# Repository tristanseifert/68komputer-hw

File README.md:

# 68komputer Hardware
Hardware designs for the 68komputer.

You can find the related software [in this repository.](https://github.com/tristanseifert/68komputer-sw)

## Old stuff
The 68008-based design I [wrote about](https://blraaz.me/hardware/2019/11/01/68komputer-it-lives.html) and some other stuff has been moved to the `old` directory. Unfortunately, those designs were done using Cadsoft EAGLE, and I no longer have access to my license for it. There are likely hardware bugs I have no way of fixing. Yay!

## License
The contents of this repo are available under the ISC license.

Previously, the material in the `old` directory was BSD licensed; you can continue to use it under the terms of this license.

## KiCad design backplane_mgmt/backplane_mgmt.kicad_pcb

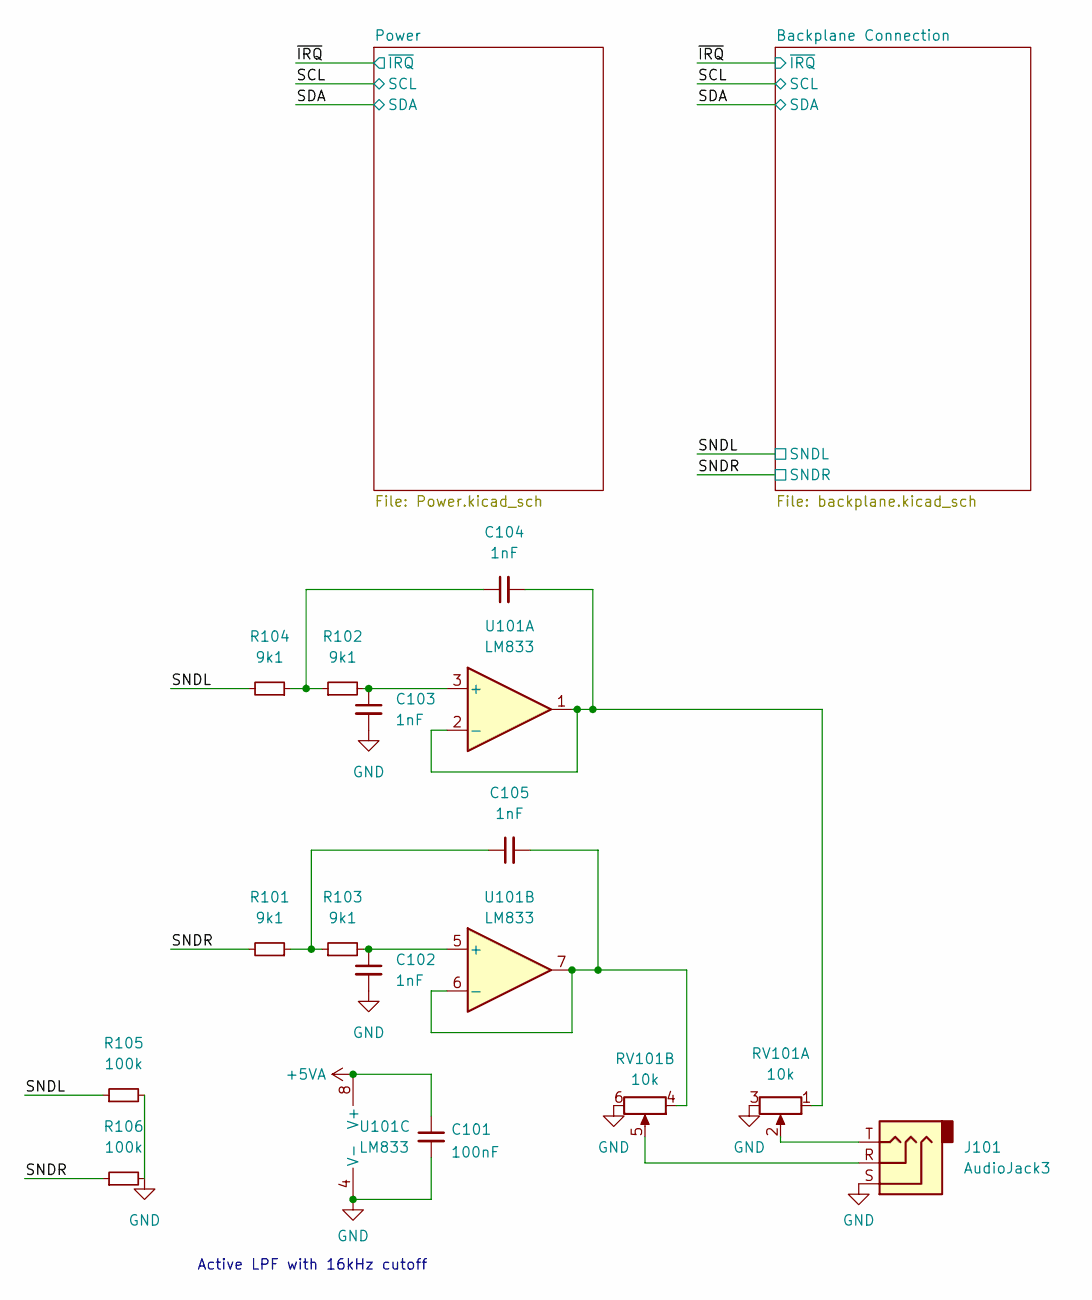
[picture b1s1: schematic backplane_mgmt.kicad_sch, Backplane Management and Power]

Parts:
C101: 100nF; C_0805_2012Metric
C102, C103, C104, C105: 1nF; C_Rect_L7.2mm_W2.5mm_P5.00mm_FKS2_FKP2_MKS2_MKP2; MPN B32529C1102J
J101: AudioJack3; Jack_3.5mm_CUI_SJ1-3533NG_Horizontal; MPN SJ1-3533NG
R101, R102, R103, R104: 9k1; R_0805_2012Metric
R105, R106: 100k; R_0805_2012Metric
RV101: 10k; Potentiometer_Alps_RK097_Dual_Horizontal
U101: LM833; DIP-8_W7.62mm_Socket

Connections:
+5VA: C101.1, U101.8 (V+); also elsewhere on the board
/SNDL: R104.2, R105.1; also elsewhere on the board
/SNDR: R101.2, R106.1; also elsewhere on the board
GND: C101.2, C102.2, C103.2, J101.S, R105.2, R106.2, RV101.3, RV101.6, U101.4 (V-); also elsewhere on the board
unnamed: C102.1, R103.2, U101.5 (+)
unnamed: C103.1, R102.2, U101.3 (+)
unnamed: C104.1, R102.1, R104.1
unnamed: C104.2, RV101.1, U101.1, U101.2 (-)
unnamed: C105.1, R101.1, R103.1
unnamed: C105.2, RV101.4, U101.6 (-), U101.7
unnamed: J101.R, RV101.5
unnamed: J101.T, RV101.2

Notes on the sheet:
Active LPF with 16kHz cutoff

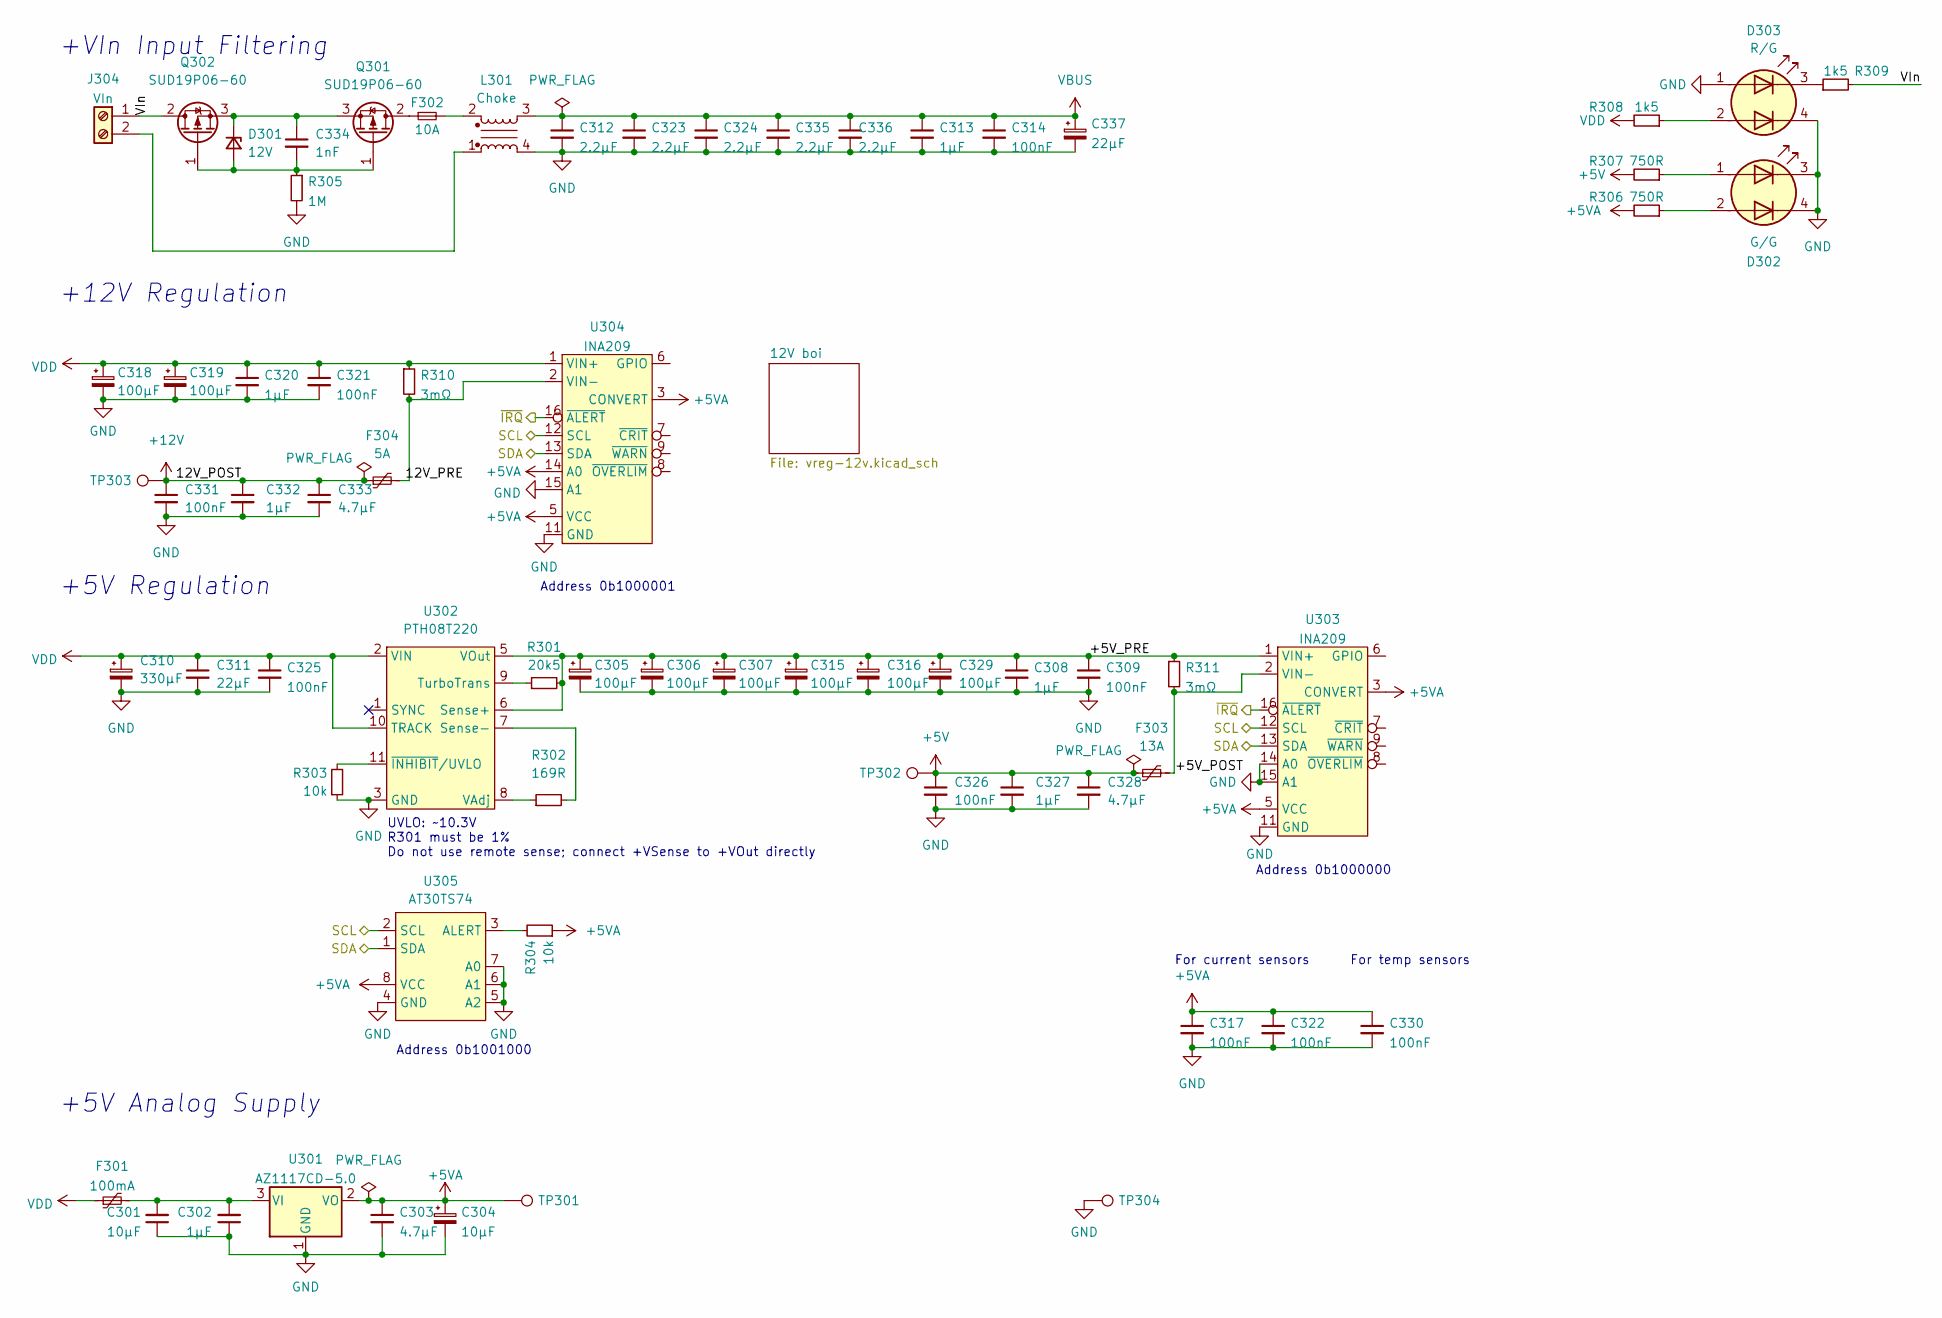
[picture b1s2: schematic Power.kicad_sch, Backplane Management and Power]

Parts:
C301: 10µF; C_0805_2012Metric
C302, C308, C313, C320, C327, C332: 1µF; C_0805_2012Metric
C303, C328, C333: 4.7µF; C_0805_2012Metric
C304: 10µF; CP_EIA-3216-18_Kemet-A; MPN TAJA106K016RNJV
C305, C306, C307, C315, C316, C329: 100µF; CP_Radial_D5.0mm_P2.00mm; MPN A750BK107M1AAAE024
C309, C314, C317, C321, C322, C325, C326, C330, C331: 100nF; C_0805_2012Metric
C310: 330µF; CP_Radial_D8.0mm_P3.50mm; MPN A750KS337M1EAAE018
C311: 22µF; C_0805_2012Metric; MPN CL21A226MAQNNNF
C312, C323, C324, C335, C336: 2.2µF; C_1206_3216Metric; MPN CL31A225KB9LNNC
C318, C319: 100µF; CP_Radial_D8.0mm_P3.50mm; MPN A750KK107M1EAAE040
C334: 1nF; C_0805_2012Metric
C337: 22µF; CP_Radial_D5.0mm_P2.00mm
D301: 12V; D_MiniMELF; MPN ZMM5242B
D302: G/G; H201Cxx; MPN H201CGDL
D303: R/G; H201Cxx; MPN H201CGHDL
F301: 100mA; Fuse_1812_4532Metric; MPN PTS181230V010
F302: 10A; Keystone-3557-2-0; MPN 3557-10
F303: 13A; Fuse_Bourns_MF-RHT1300; MPN MF-RHT1300-0
F304: 5A; Fuse_Bourns_MF-RHT500; MPN MF-RHT500-2
J304: VIn; CUI_TBP01R1W-508-02BE; MPN TBP01R1W-508-02BE
L301: Choke; TDK-ACM1513-0-0-MFG; MPN ACM1513-551-2PL-TLHF
Q301, Q302: SUD19P06-60; TO-252-2; MPN SUD19P06-60-GE3
R301: 20k5; R_0805_2012Metric
R302: 169R; R_0805_2012Metric
R303, R304: 10k; R_0805_2012Metric
R305: 1M; R_0805_2012Metric
R306, R307: 750R; R_0805_2012Metric
R308, R309: 1k5; R_0805_2012Metric
R310, R311: 3mΩ; R_2512_6332Metric_Pad1.40x3.35mm_HandSolder; MPN LRMAP2512-R003FT4
TP301: +5VA; TestPoint_Loop_D2.60mm_Drill1.4mm_Beaded; MPN 534-5001
TP302: +5V; TestPoint_Loop_D2.60mm_Drill1.4mm_Beaded; MPN 534-5001
TP303: +12V; TestPoint_Loop_D2.60mm_Drill1.4mm_Beaded; MPN 534-5001
TP304: GND; TestPoint_Loop_D2.60mm_Drill1.4mm_Beaded; MPN 534-5001
U301: AZ1117CD-5.0; TO-252-2
U302: PTH08T220; Texas_Instruments-PTH08T220WAD-Manufacturer_Recommended
U303, U304: INA209; TSSOP-16_4.4x5mm_P0.65mm
U305: AT30TS74; MSOP-8_3x3mm_P0.65mm

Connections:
+5V: C326.1, C327.1, C328.1, F303.1, R307.2, TP302.1; also elsewhere on the board
+5VA: C303.1, C304.1, C317.1, C322.1, C330.1, R304.1, R306.2, TP301.1, U301.2 (VO), U303.3 (CONVERT), U303.5 (VCC), U303.10 (VCC), U304.3 (CONVERT), U304.5 (VCC), U304.10 (VCC), U304.14 (A0), U305.8 (VCC); also elsewhere on the board
+12V: C331.1, C332.1, C333.1, F304.1, TP303.1; also elsewhere on the board
/Power/12V_PRE: F304.2, R310.2, U304.2 (VIN-)
/Power/+5V_POST: F303.2, R311.2, U303.2 (VIN-)
/Power/+5V_PRE: C305.1, C306.1, C307.1, C308.1, C309.1, C315.1, C316.1, C329.1, R301.2, R311.1, U302.5 (VOut), U302.6 (Sense+), U303.1 (VIN+)
/Power/VIn: J304.1, Q302.2 (D), R309.2
/SCL: U303.12 (SCL), U304.12 (SCL), U305.2 (SCL); also elsewhere on the board
/SDA: U303.13 (SDA), U304.13 (SDA), U305.1 (SDA); also elsewhere on the board
/~IRQ: U303.16 (~ALERT), U304.16 (~ALERT); also elsewhere on the board
GND: C301.1, C302.1, C303.2, C304.2, C305.2, C306.2, C307.2, C308.2, C309.2, C310.2, C311.2, C312.2, C313.2, C314.2, C315.2, C316.2, C317.2, C318.2, C319.2, C320.2, C321.2, C322.2, C323.2, C324.2, C325.2, C326.2, C327.2, C328.2, C329.2, C330.2, C331.2, C332.2, C333.2, C335.2, C336.2, C337.2, D302.3 (K1), D302.4 (K2), D303.1 (A1), D303.4 (K2), L301.4, R303.1, R305.2, TP304.1, U301.1 (GND), U302.3 (GND), U302.4 (GND), U303.4 (GND), U303.11 (GND), U303.14 (A0), U303.15 (A1), U304.4 (GND), U304.11 (GND), U304.15 (A1), U305.4 (GND), U305.5 (A2), U305.6 (A1), U305.7 (A0); also elsewhere on the board
unnamed: C301.2, C302.2, F301.2, U301.3 (VI)
unnamed: C334.1, D301.1 (K), Q301.3 (S), Q302.3 (S)
unnamed: C334.2, D301.2 (A), Q301.1 (G), Q302.1 (G), R305.1
unnamed: D302.1 (A1), R307.1
unnamed: D302.2 (A2), R306.1
unnamed: D303.2 (A2), R308.1
unnamed: D303.3 (K1), R309.1
unnamed: F302.1, Q301.2 (D)
unnamed: F302.2, L301.2
unnamed: J304.2, L301.1
unnamed: R301.1, U302.9 (TurboTrans)
unnamed: R302.1, U302.8 (VAdj)
unnamed: R302.2, U302.7 (Sense-)
unnamed: R303.2, U302.11 (~INHIBIT/UVLO)
unnamed: R304.2, U305.3 (ALERT)
VBUS: C312.1, C313.1, C314.1, C323.1, C324.1, C335.1, C336.1, C337.1, L301.3; also elsewhere on the board
VDD: C310.1, C311.1, C318.1, C319.1, C320.1, C321.1, C325.1, F301.1, R308.2, R310.1, U302.2 (VIN), U302.10 (TRACK), U304.1 (VIN+); also elsewhere on the board

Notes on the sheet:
+5V Regulation
Address 0b1000000
+12V Regulation
Address 0b1001000
+5V Analog Supply
Address 0b1000001
For temp sensors
UVLO: ~10.3V R301 must be 1% Do not use remote sense; connect +VSense to +VOut directly
+VIn Input Filtering
For current sensors

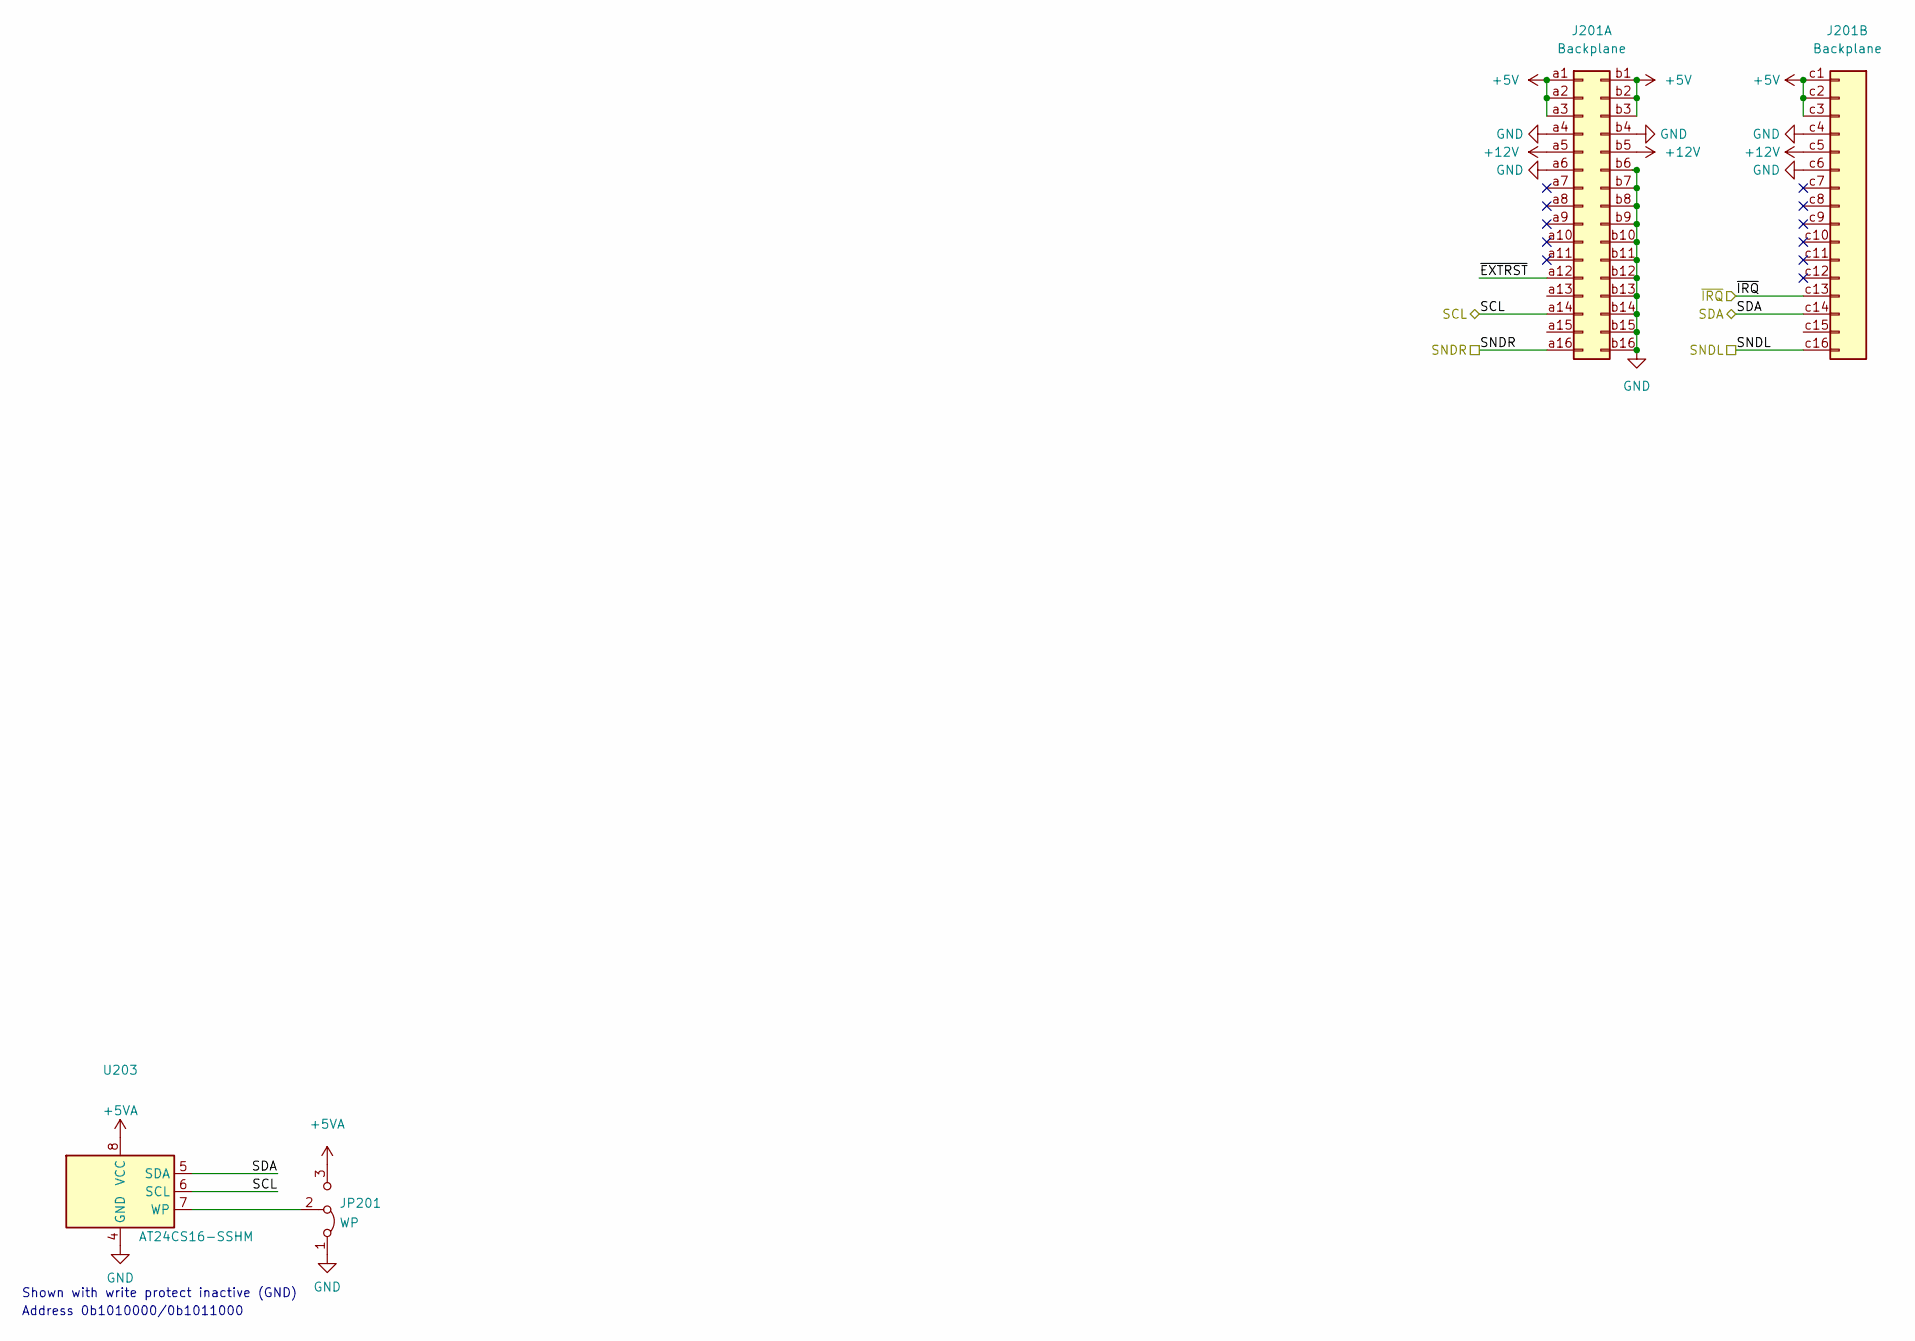
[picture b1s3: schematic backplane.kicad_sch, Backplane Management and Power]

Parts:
J201: Backplane; DIN41612_C2_3x16_Male_Horizontal_THT
JP201: WP; SolderJumper-3_P1.3mm_Bridged2Bar12_Pad1.0x1.5mm
U203: AT24CS16-SSHM; SOIC-8_3.9x4.9mm_P1.27mm; MPN AT24CS32-SSHM-T

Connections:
+5V: J201.a1, J201.a2, J201.a3, J201.b1, J201.b2, J201.b3, J201.c1, J201.c2, J201.c3; also elsewhere on the board
+5VA: JP201.3 (B), U203.8 (VCC); also elsewhere on the board
+12V: J201.a5, J201.b5, J201.c5; also elsewhere on the board
/Backplane Connection/~EXTRST: J201.a12
/SCL: J201.a14, U203.6 (SCL); also elsewhere on the board
/SDA: J201.c14, U203.5 (SDA); also elsewhere on the board
/SNDL: J201.c16; also elsewhere on the board
/SNDR: J201.a16; also elsewhere on the board
/~IRQ: J201.c13; also elsewhere on the board
GND: J201.a4, J201.a6, J201.b4, J201.b6, J201.b7, J201.b8, J201.b9, J201.b10, J201.b11, J201.b12, J201.b13, J201.b14, J201.b15, J201.b16, J201.c4, J201.c6, JP201.1 (A), U203.4 (GND); also elsewhere on the board
unnamed: JP201.2 (C), U203.7 (WP)

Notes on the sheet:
Shown with write protect inactive (GND)
Address 0b1010000/0b1011000

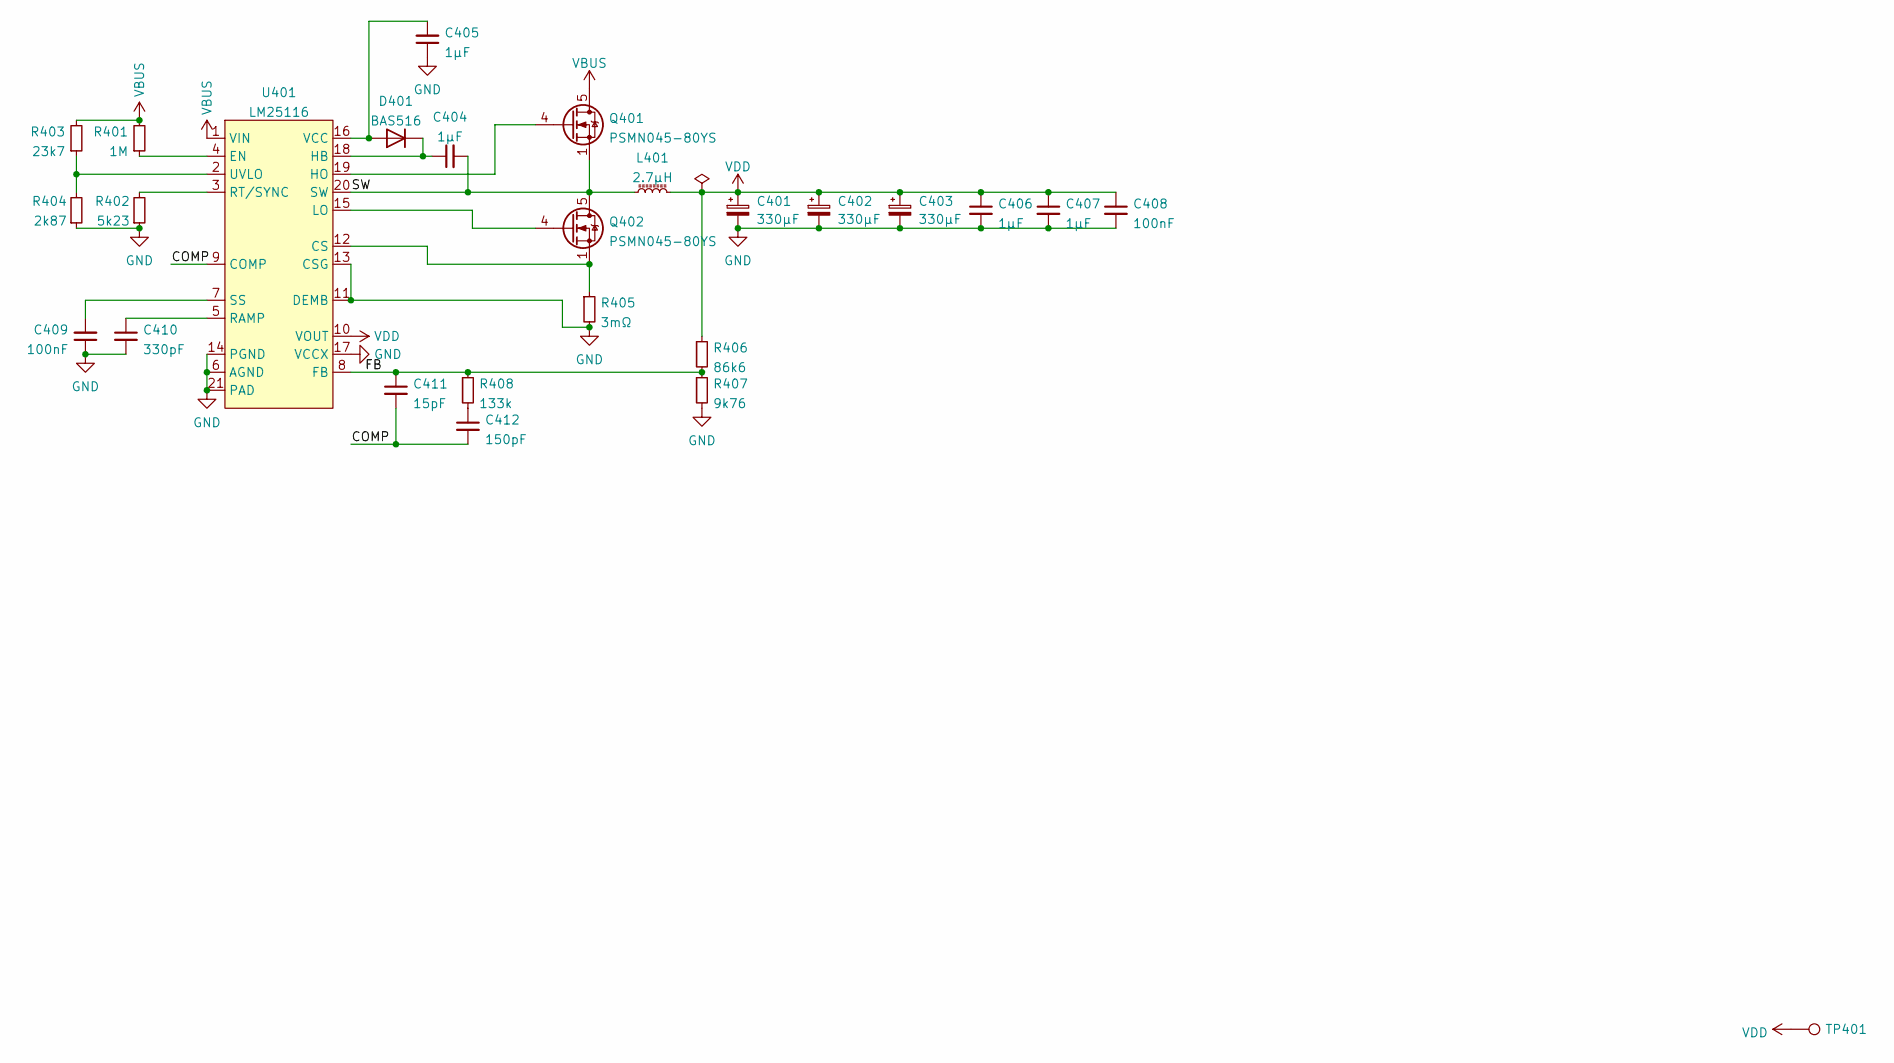
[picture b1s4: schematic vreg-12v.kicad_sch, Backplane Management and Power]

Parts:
C401, C402, C403: 330µF; CP_Radial_D8.0mm_P3.50mm; MPN 860010474012
C404, C405, C406, C407: 1µF; C_0805_2012Metric
C408, C409: 100nF; C_0805_2012Metric
C410: 330pF; C_0805_2012Metric
C411: 15pF; C_0805_2012Metric; MPN 885012007052
C412: 150pF; C_0805_2012Metric; MPN 885012207081
D401: BAS516; D_SOD-523; MPN BAS516-TP
L401: 2.7µH; Bourns_Inc.-SRP1250-0-0-MFG; MPN SRP1250-2R7M
Q401, Q402: PSMN045-80YS; LFPAK56; MPN PSMN045-80YS,115
R401: 1M; R_0805_2012Metric
R402: 5k23; R_0805_2012Metric; MPN CR0805-FX-5231ELF
R403: 23k7; R_0805_2012Metric; MPN CR0805-FX-5231ELF
R404: 2k87; R_0805_2012Metric; MPN CR0805-FX-5231ELF
R405: 3mΩ; R_2512_6332Metric_Pad1.40x3.35mm_HandSolder; MPN LRMAP2512-R003FT4
R406: 86k6; R_0805_2012Metric; MPN RC0805FR-0786K6L
R407: 9k76; R_0805_2012Metric; MPN RC0805FR-079K76L
R408: 133k; R_0805_2012Metric
TP401: VDD; TestPoint_Loop_D2.60mm_Drill1.4mm_Beaded; MPN 534-5001
U401: LM25116; HTSSOP-20-1EP_4.4x6.5mm_P0.65mm_EP2.85x4mm

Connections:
/Power/12V boi/COMP: C411.2, C412.2, U401.9 (COMP)
/Power/12V boi/FB: C411.1, R406.2, R407.1, R408.1, U401.8 (FB)
/Power/12V boi/SW: C404.2, L401.1, Q401.1 (S), Q401.2 (S), Q401.3 (S), Q402.5 (D), U401.20 (SW)
GND: C401.2, C402.2, C403.2, C405.1, C406.2, C407.2, C408.2, C409.1, C410.2, R402.1, R404.1, R405.2, R407.2, U401.6 (AGND), U401.11 (DEMB), U401.13 (CSG), U401.14 (PGND), U401.17 (VCCX), U401.21 (PAD); also elsewhere on the board
unnamed: C404.1, D401.1 (K), U401.18 (HB)
unnamed: C405.2, D401.2 (A), U401.16 (VCC)
unnamed: C409.2, U401.7 (SS)
unnamed: C410.1, U401.5 (RAMP)
unnamed: C412.1, R408.2
unnamed: Q401.4 (G), U401.19 (HO)
unnamed: Q402.1 (S), Q402.2 (S), Q402.3 (S), R405.1, U401.12 (CS)
unnamed: Q402.4 (G), U401.15 (LO)
unnamed: R401.1, U401.4 (EN)
unnamed: R402.2, U401.3 (RT/SYNC)
unnamed: R403.1, R404.2, U401.2 (UVLO)
VBUS: Q401.5 (D), R401.2, R403.2, U401.1 (VIN); also elsewhere on the board
VDD: C401.1, C402.1, C403.1, C406.1, C407.1, C408.1, L401.2, R406.1, TP401.1, U401.10 (VOUT); also elsewhere on the board

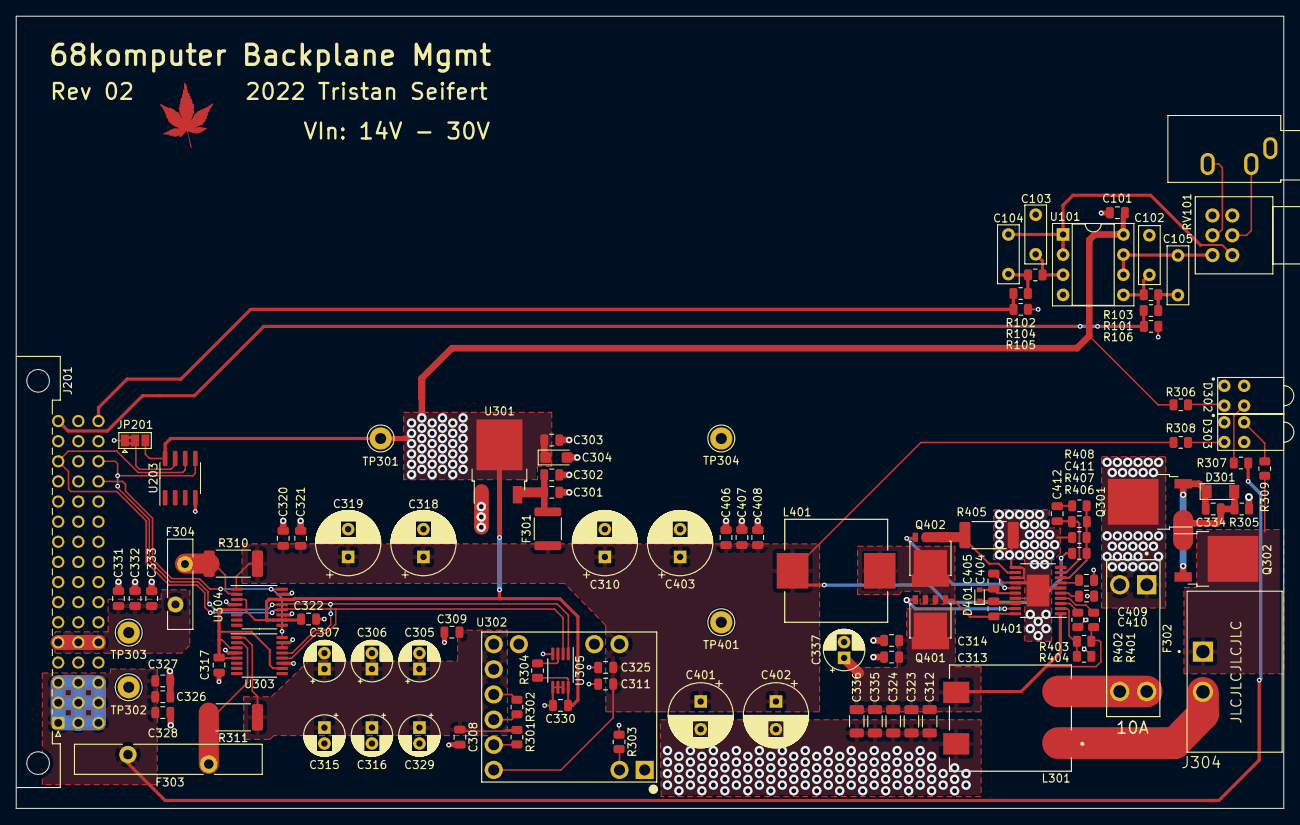
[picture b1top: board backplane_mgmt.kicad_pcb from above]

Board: 2 copper layers, 160.0 x 100.0 mm, 111 parts (0 on the bottom side), 53 nets.

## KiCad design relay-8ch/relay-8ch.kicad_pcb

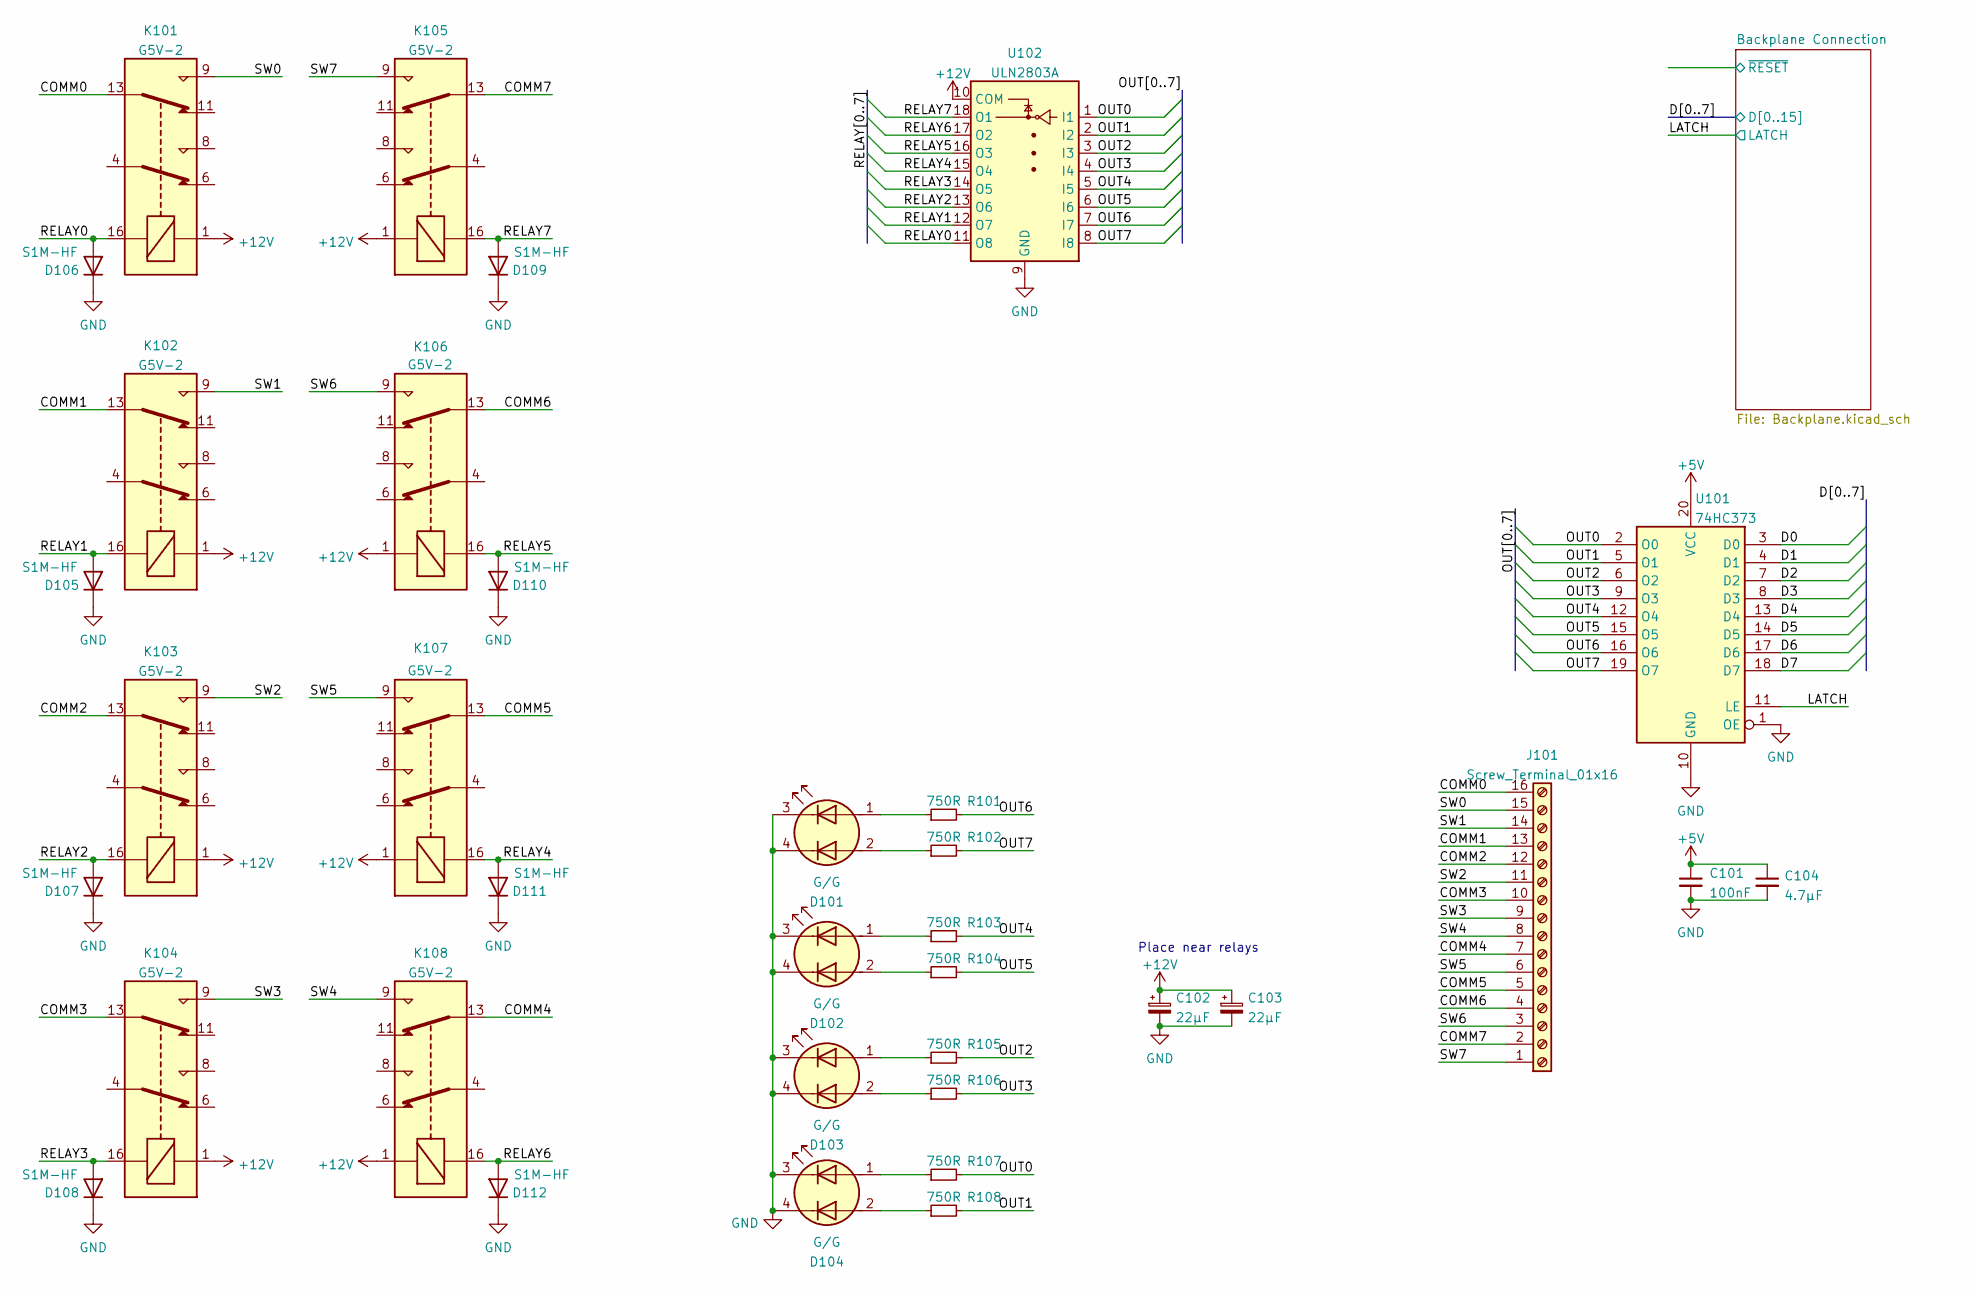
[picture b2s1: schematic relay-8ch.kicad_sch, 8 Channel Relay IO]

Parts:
C101: 100nF; C_0805_2012Metric
C102, C103: 22µF; CP_Radial_D6.3mm_P2.50mm; MPN A759EK226M1JAAE054
C104: 4.7µF; C_0805_2012Metric
D101, D102, D103, D104: G/G; H201Cxx; MPN H201CGDL
D105, D106, D107, D108, D109, D110, D111, D112: S1M-HF; D_SMA; MPN S1M-HF
J101: Screw_Terminal_01x16; CUI_TBP02R1W-381-16BE; MPN TBP02R1W-381-16BE
K101, K102, K103, K104, K105, K106, K107, K108: G5V-2; Relay_DPDT_Omron_G5V-2
R101, R102, R103, R104, R105, R106, R107, R108: 750R; R_0805_2012Metric
U101: 74HC373; SOIC-20W_7.5x12.8mm_P1.27mm
U102: ULN2803A; DIP-18_W7.62mm_Socket

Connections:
+5V: C101.1, C104.1, U101.20 (VCC); also elsewhere on the board
+12V: C102.1, C103.1, K101.1, K102.1, K103.1, K104.1, K105.1, K106.1, K107.1, K108.1, U102.10 (COM); also elsewhere on the board
/COMM0: J101.16, K101.13
/COMM1: J101.13, K102.13
/COMM2: J101.12, K103.13
/COMM3: J101.10, K104.13
/COMM4: J101.7, K108.13
/COMM5: J101.5, K107.13
/COMM6: J101.4, K106.13
/COMM7: J101.2, K105.13
/D0: U101.3 (D0); also elsewhere on the board
/D1: U101.4 (D1); also elsewhere on the board
/D2: U101.7 (D2); also elsewhere on the board
/D3: U101.8 (D3); also elsewhere on the board
/D4: U101.13 (D4); also elsewhere on the board
/D5: U101.14 (D5); also elsewhere on the board
/D6: U101.17 (D6); also elsewhere on the board
/D7: U101.18 (D7); also elsewhere on the board
/LATCH: U101.11 (LE); also elsewhere on the board
/OUT0: R107.2, U101.2 (O0), U102.1 (I1)
/OUT1: R108.2, U101.5 (O1), U102.2 (I2)
/OUT2: R105.2, U101.6 (O2), U102.3 (I3)
/OUT3: R106.2, U101.9 (O3), U102.4 (I4)
/OUT4: R103.2, U101.12 (O4), U102.5 (I5)
/OUT5: R104.2, U101.15 (O5), U102.6 (I6)
/OUT6: R101.2, U101.16 (O6), U102.7 (I7)
/OUT7: R102.2, U101.19 (O7), U102.8 (I8)
/RELAY0: D106.2 (A), K101.16, U102.11 (O8)
/RELAY1: D105.2 (A), K102.16, U102.12 (O7)
/RELAY2: D107.2 (A), K103.16, U102.13 (O6)
/RELAY3: D108.2 (A), K104.16, U102.14 (O5)
/RELAY4: D111.2 (A), K107.16, U102.15 (O4)
/RELAY5: D110.2 (A), K106.16, U102.16 (O3)
/RELAY6: D112.2 (A), K108.16, U102.17 (O2)
/RELAY7: D109.2 (A), K105.16, U102.18 (O1)
/SW0: J101.15, K101.9
/SW1: J101.14, K102.9
/SW2: J101.11, K103.9
/SW3: J101.9, K104.9
/SW4: J101.8, K108.9
/SW5: J101.6, K107.9
/SW6: J101.3, K106.9
/SW7: J101.1, K105.9
GND: C101.2, C102.2, C103.2, C104.2, D101.3 (K1), D101.4 (K2), D102.3 (K1), D102.4 (K2), D103.3 (K1), D103.4 (K2), D104.3 (K1), D104.4 (K2), D105.1 (K), D106.1 (K), D107.1 (K), D108.1 (K), D109.1 (K), D110.1 (K), D111.1 (K), D112.1 (K), U101.1 (OE), U101.10 (GND), U102.9 (GND); also elsewhere on the board
unnamed: D101.1 (A1), R101.1
unnamed: D101.2 (A2), R102.1
unnamed: D102.1 (A1), R103.1
unnamed: D102.2 (A2), R104.1
unnamed: D103.1 (A1), R105.1
unnamed: D103.2 (A2), R106.1
unnamed: D104.1 (A1), R107.1
unnamed: D104.2 (A2), R108.1

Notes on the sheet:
Place near relays
